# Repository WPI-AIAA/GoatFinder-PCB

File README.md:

# Goat Finder PCB
### PCB Files for Goat Finder

Made using Eagle 8.4.1 Premium

**Run `make clean` before pushing!**

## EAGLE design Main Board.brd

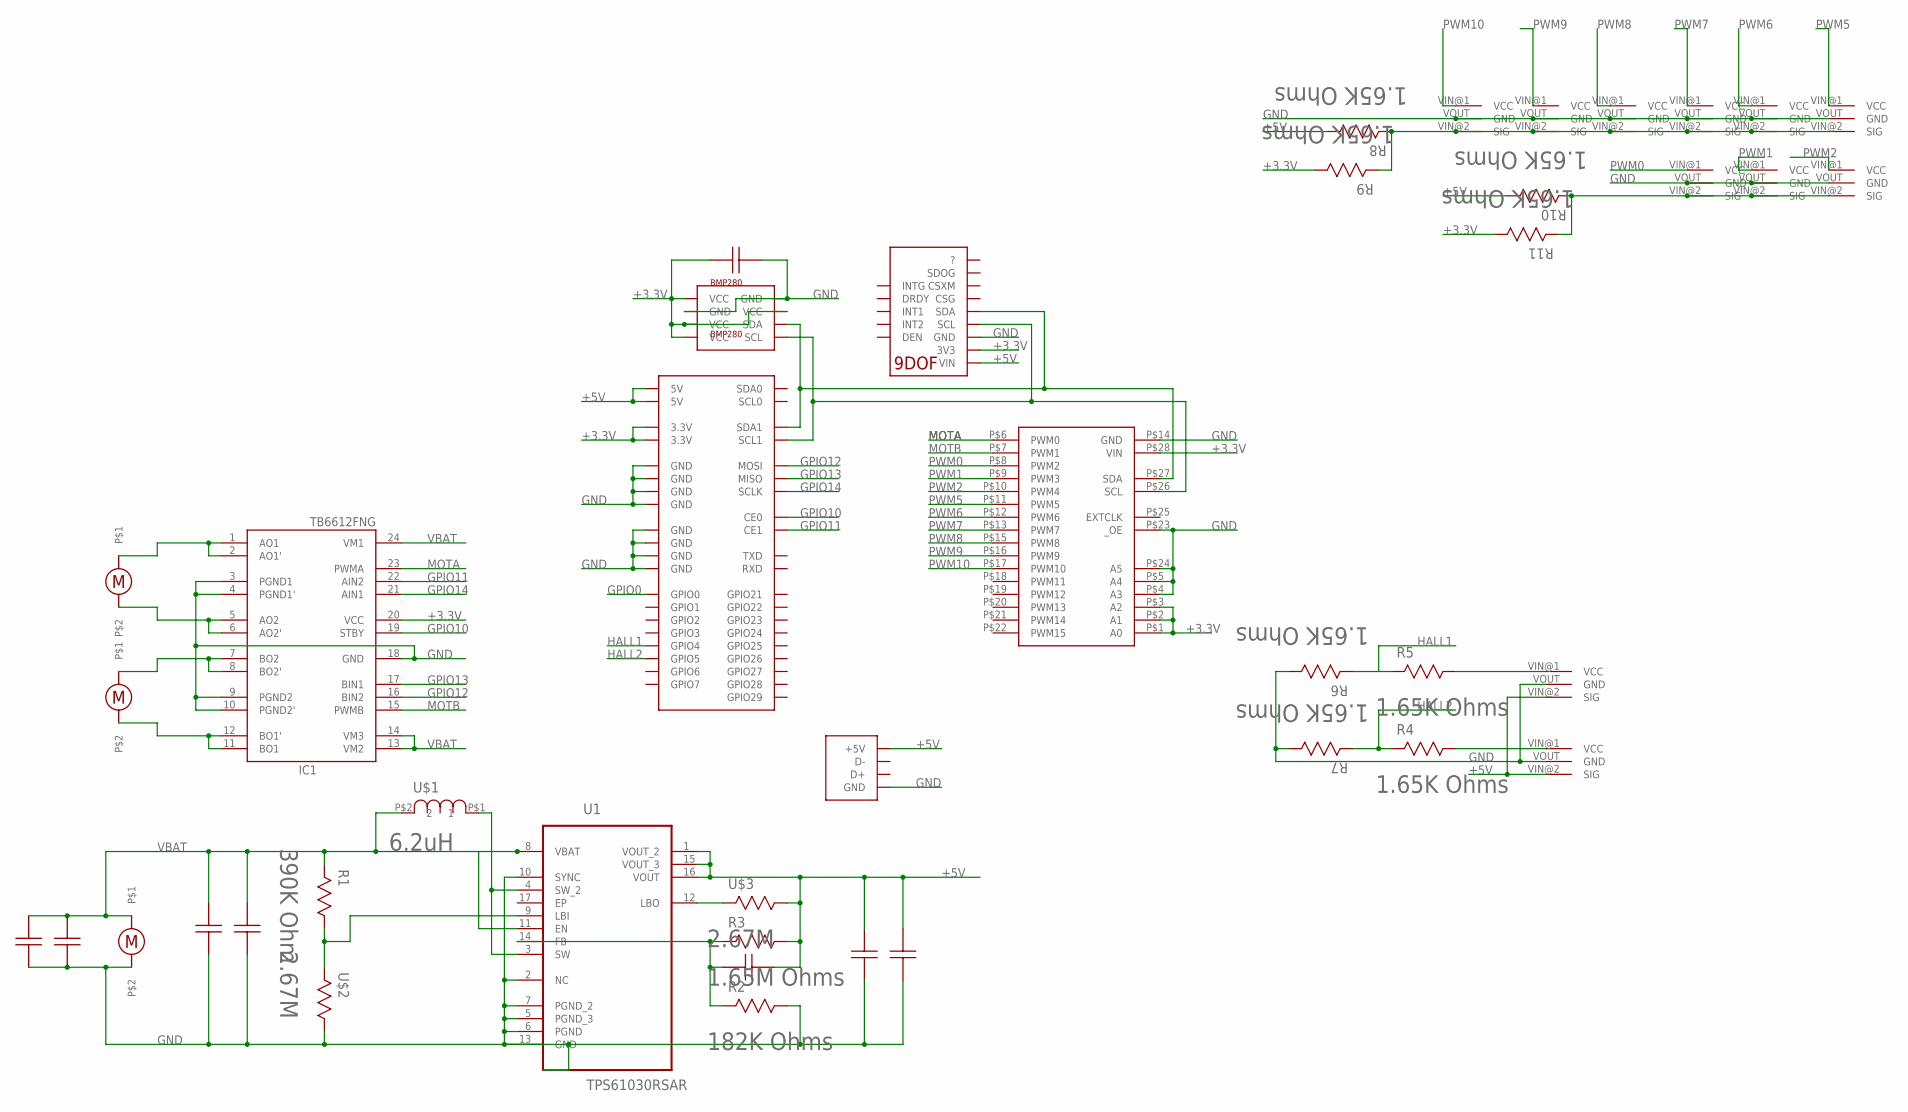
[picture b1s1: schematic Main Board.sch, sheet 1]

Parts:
IC1: TB6612FNG; SSOP24
R1: 390K Ohm; RESC2013X65N
R2: 182K Ohms; RESC2013X65N
R3: 1.65M Ohms; RESC1608X60N
R4, R5, R6, R7, R8, R9, R10, R11: 1.65K Ohms; RESC1608X60N
U1: TPS61030RSAR; QFN65P400X400X100-17N
U$1: 6.2uH; SRU1038-6R2Y
U$2, U$3: 2.67M; RESC1005X40N
U$4: 10pF; 0603
U$5, U$20, U$21: MOTOR; MOTOR_PAD
U$6: 9DOF
U$7, U$14: 0603CAP; 0603
U$8: USB_VERTICLE
U$9, U$10: 0805CAP; RESC2013X45N
U$11: PI; PI_HEADER_SMD
U$12, U$18, U$19: 220
U$13: BMP280
U$15, U$16, U$17, U$22, U$23, U$24, U$25, U$26, U$28, U$29, U$30: PJUMP; JUMPER
U$27: PWM; TSSOP28

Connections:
+3.3V: IC1.20 (VCC), R9.1, R11.1, U$6.P$21 (3V3), U$11.3.3V@1 (3.3V), U$11.3.3V@17 (3.3V), U$13.P$2 (VCC), U$13.P$5 (VCC), U$13.P$6 (VCC), U$13.P$8 (VCC), U$14.P$1, U$27.P$1 (A0), U$27.P$2 (A1), U$27.P$3 (A2), U$27.P$28 (VIN)
+5V: R3.1, R8.1, R10.1, U1.1 (VOUT_2), U1.15 (VOUT_3), U1.16 (VOUT), U$3.1, U$4.P$2, U$6.P$20 (VIN), U$8.VCC (+5V), U$9.1, U$11.5V@2 (5V), U$11.5V@4 (5V), U$12.P$1, U$15.VIN@2 (SIG), U$16.VIN@2 (SIG)
GND: IC1.3 (PGND1), IC1.4 (PGND1'), IC1.9 (PGND2), IC1.10 (PGND2'), IC1.18 (GND), R2.1, R6.1, R7.1, U1.2 (NC), U1.5 (PGND_3), U1.6 (PGND), U1.7 (PGND_2), U1.10 (SYNC), U1.13 (GND), U$2.1, U$6.P$22 (GND), U$7.P$2, U$8.GND@1 (GND), U$8.GND@2 (GND), U$8.GND@3 (GND), U$9.2, U$10.2, U$11.GND@6 (GND), U$11.GND@9 (GND), U$11.GND@14 (GND), U$11.GND@20 (GND), U$11.GND@25 (GND), U$11.GND@30 (GND), U$11.GND@34 (GND), U$11.GND@39 (GND), U$12.P$2, U$13.P$1 (GND), U$13.P$7 (GND), U$14.P$2, U$15.VOUT (GND), U$16.VOUT (GND), U$17.VOUT (GND), U$18.P$2, U$19.P$2, U$21.P$2, U$22.VOUT (GND), U$23.VOUT (GND), U$24.VOUT (GND), U$25.VOUT (GND), U$26.VOUT (GND), U$27.P$4 (A3), U$27.P$5 (A4), U$27.P$14 (GND), U$27.P$23 (_OE), U$27.P$24 (A5), U$28.VOUT (GND), U$29.VOUT (GND), U$30.VOUT (GND)
GPIO0: U$11.GPIO0
GPIO10: IC1.19 (STBY), U$11.CE0
GPIO11: IC1.22 (AIN2), U$11.CE1
GPIO12: IC1.16 (BIN2), U$11.MOSI
GPIO13: IC1.17 (BIN1), U$11.MISO
GPIO14: IC1.21 (AIN1), U$11.SCLK
HALL1: R5.2, R6.2, U$11.GPIO4
HALL2: R4.2, R7.2, U$11.GPIO5
MOTA: IC1.23 (PWMA), U$27.P$6 (PWM0)
MOTB: IC1.15 (PWMB), U$27.P$7 (PWM1)
unnamed: R1.1, U1.9 (LBI), U$2.2
unnamed: U1.3 (SW), U1.4 (SW_2), U$1.P$1 (1)
unnamed: R8.2, R9.2, U$17.VIN@2 (SIG), U$22.VIN@2 (SIG), U$23.VIN@2 (SIG), U$24.VIN@2 (SIG), U$25.VIN@2 (SIG), U$26.VIN@2 (SIG)
unnamed: R5.1, U$15.VIN@1 (VCC)
unnamed: R4.1, U$16.VIN@1 (VCC)
unnamed: U1.12 (LBO), U$3.2
unnamed: R10.2, R11.2, U$28.VIN@2 (SIG), U$29.VIN@2 (SIG), U$30.VIN@2 (SIG)
unnamed: U$6.P$23 (SCL), U$11.SCL1, U$13.P$4 (SCL), U$27.P$26 (SCL)
unnamed: R2.2, R3.2, U1.14 (FB), U$4.P$1
unnamed: U$6.P$24 (SDA), U$11.SDA1, U$13.P$3 (SDA), U$27.P$27 (SDA)
unnamed: IC1.1 (AO1), IC1.2 (AO1'), U$20.P$1
unnamed: IC1.5 (AO2), IC1.6 (AO2'), U$20.P$2
unnamed: IC1.7 (BO2), IC1.8 (BO2'), U$5.P$1
unnamed: IC1.11 (BO1), IC1.12 (BO1'), U$5.P$2
PWM0: U$27.P$8 (PWM2), U$30.VIN@1 (VCC)
PWM1: U$27.P$9 (PWM3), U$29.VIN@1 (VCC)
PWM2: U$27.P$10 (PWM4), U$28.VIN@1 (VCC)
PWM5: U$17.VIN@1 (VCC), U$27.P$11 (PWM5)
PWM6: U$22.VIN@1 (VCC), U$27.P$12 (PWM6)
PWM7: U$23.VIN@1 (VCC), U$27.P$13 (PWM7)
PWM8: U$24.VIN@1 (VCC), U$27.P$15 (PWM8)
PWM9: U$25.VIN@1 (VCC), U$27.P$16 (PWM9)
PWM10: U$26.VIN@1 (VCC), U$27.P$17 (PWM10)
VBAT: IC1.13 (VM2), IC1.14 (VM3), IC1.24 (VM1), R1.2, U1.8 (VBAT), U1.11 (EN), U$1.P$2 (2), U$7.P$1, U$10.1, U$18.P$1, U$19.P$1, U$21.P$1

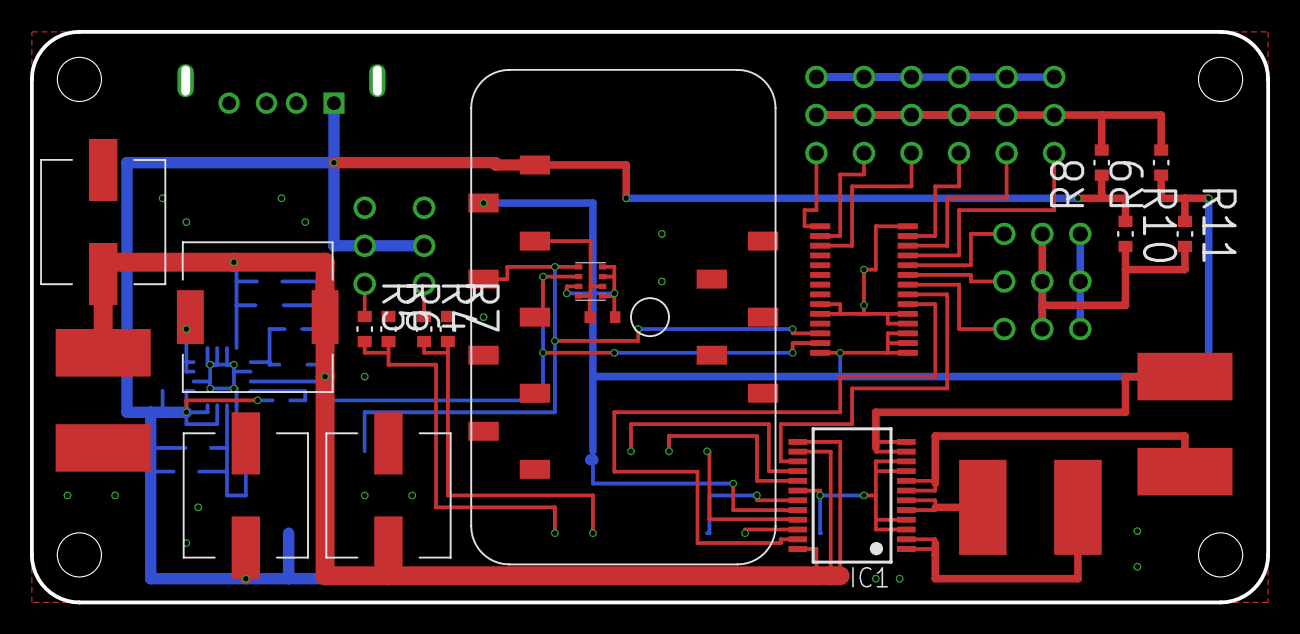
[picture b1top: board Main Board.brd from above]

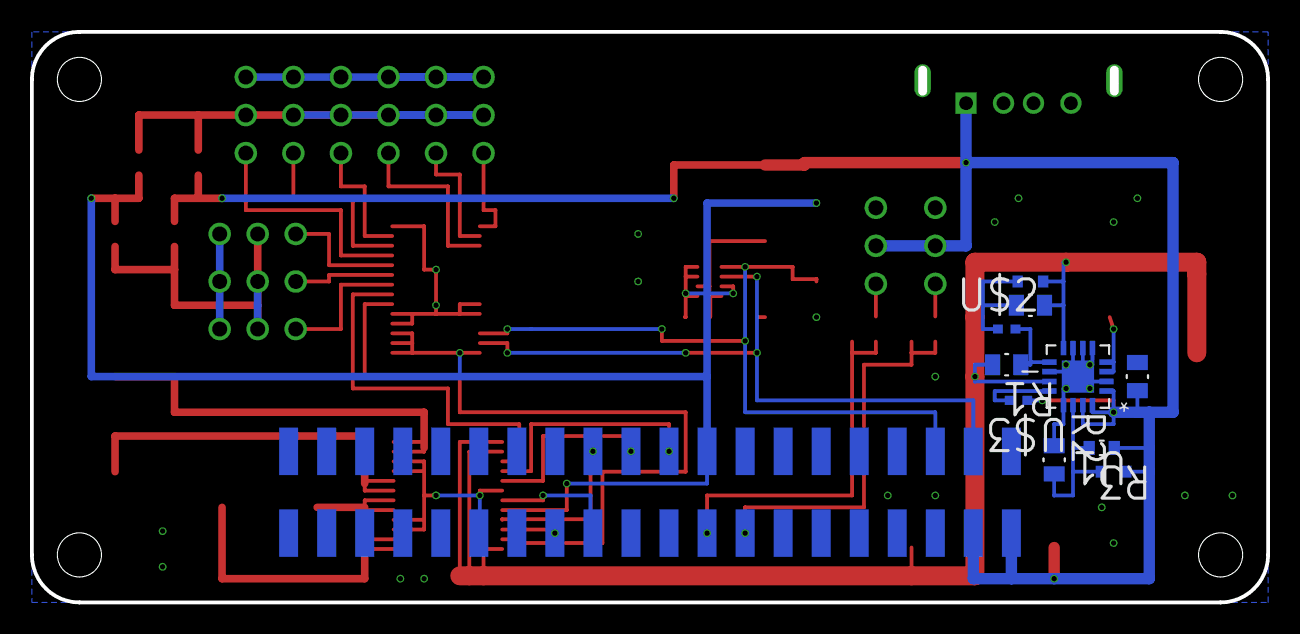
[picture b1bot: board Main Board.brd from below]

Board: 2 copper layers, 82.5 x 38.1 mm, 43 parts (11 on the bottom side), 36 nets.

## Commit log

2017-11-06 Added Initial Board and Schematic Files
2017-11-07 Added Texas Instruments Library
2017-11-07 Added Vishay and Bourns part libraries
2017-11-07 Finished +5V Power Supply Schematic
2017-11-07 Completed Barometer / Altitude Schematic
2017-11-07 Completed Motor Driver schematic
2017-11-08 Modified part placment
2017-11-10 Reduced Board Size and added Ground Planes
2017-11-10 Components in place, beginning traces.
2017-11-12 Added Ground Pours
2017-11-12 Beginning Traces
2017-11-12 Power Supply Routing Complete
2018-03-19 Whatever man
